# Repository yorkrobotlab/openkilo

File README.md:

# OpenKilo

This repository contains resources related to the OpenKilo Kilobot revision, which was designed to aid repair and extensibility of the Kilobot platform.

This project was possible due to the material made open-source by other institutions, most importantly [Harvard University](https://ssr.seas.harvard.edu/kilobots) and [Western Carolina University](https://kilobot.wcu.edu/).

## Contents

* [Hardware Design](Hardware%20Design/) - KiCad project and exported Gerber files used to produce this version of the Kilobot
* [Documentation](Documentation/) - hardware schematic (produced from Harvard and WCU designs), assembly and programming guides, and bill of materials
* [Photos and Video](Photos%20and%20Video/) - showing the completed robots and their usage

## Requirements

Our Overhead Controller (OHC) was built to a design by Western Carolina University (WCU). Their detailed guide was also used for the programming and control of both the OHC and Kilobots. For more details, refer to their material at https://kilobot.wcu.edu/.

In particular:

* OHC Gerber files
* Software folder including Kilobot and OHC firmware
* [KiloGUI](https://github.com/acornejo/kilogui), GUI application for Kilobot control
* [Maker: A Kilobot Swarm](https://www.asee.org/public/conferences/64/papers/15441/view)

### Editing the PCB
[KiCad EDA](http://kicad.org/) is a free open-source electronic CAD suite which was used to create the OpenKilo design. KiCad is required in order to make changes to the design, but the exported Gerber files are also available for use directly.

The included Kilobot.lib is required for certain symbols and footprints, and must be added to the KiCad project using the process described [here](https://forum.kicad.info/t/library-management-in-kicad-version-5/14636).

[freeRouting](https://freerouting.org/) was used in conjunction with KiCad to carry out automatic PCB routing for the current design.

## Build Process
1. Purchase all PCBs and required components using BOMs included here. For the OHC PCB, use WCU Gerber files.

2. Following the guide in [Maker: A Kilobot Swarm](https://www.asee.org/public/conferences/64/papers/15441/view), install the required software before assembling the OHC and programming its firmware.

3. Assemble the OpenKilo hardware using the included assembly diagram and checklists.

4. Continuing with the WCU guide, program Kilobot firmware using a 2x3 header cable. Connection details are given in [Programming Reference.pdf](Documentation/Programming%20Reference.pdf).

5. Install KiloGUI and use the OHC to program a benchmark test onto the OpenKilo robots. These tests can be found in the WCU materials as well as at [Kilobotics](https://www.kilobotics.com/labs) where details of their functions are available.

## Author
The main OpenKilo design and prototyping was completed by Jamie Trump while a postgraduate student in the [School of Engineering, Computing and Mathematics](https://www.plymouth.ac.uk/schools/school-of-engineering-computing-and-mathematics) at the [University of Plymouth](https://www.plymouth.ac.uk/).

His original project repository can be found at [github.com/jamie-trump/Plymouth-Kilobot-2019](https://github.com/jamie-trump/Plymouth-Kilobot-2019).

This work is licensed under a [Creative Commons Attribution-NonCommercial-ShareAlike 4.0 International License](http://creativecommons.org/licenses/by-nc-sa/4.0/).

## Links

### Information and Publications
* [Kilobot @ WCU](https://kilobot.wcu.edu/)
* [Maker: A Kilobot Swarm](https://www.asee.org/public/conferences/64/papers/15441/view)
* [Kilobotics Labs](https://www.kilobotics.com/labs)

### Software
* [KiloGUI](https://github.com/acornejo/kilogui)
* [KiCad EDA](http://kicad.org/)
* [freeRouting](https://freerouting.org/)

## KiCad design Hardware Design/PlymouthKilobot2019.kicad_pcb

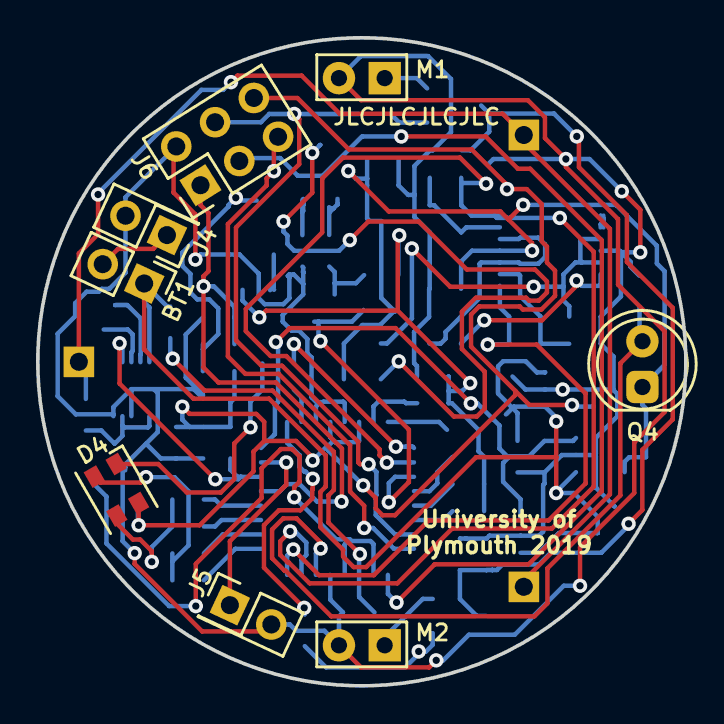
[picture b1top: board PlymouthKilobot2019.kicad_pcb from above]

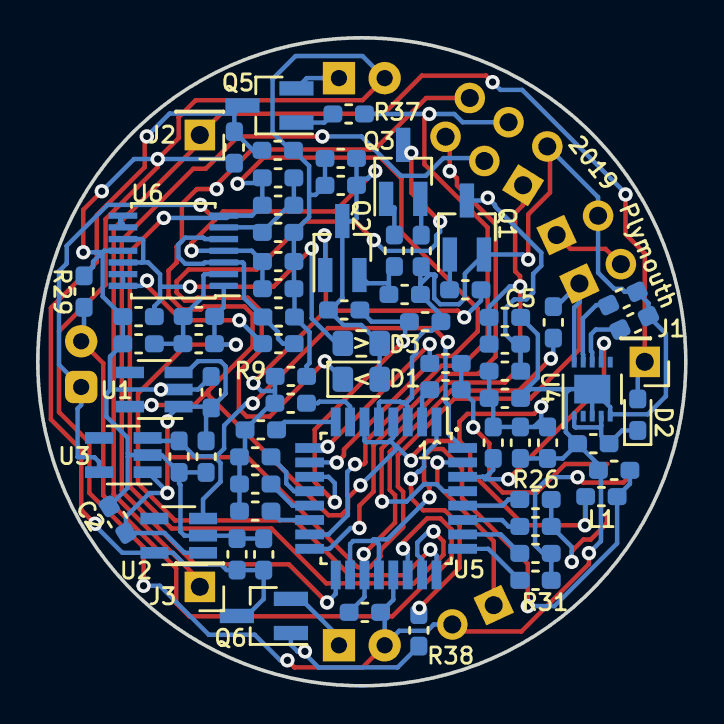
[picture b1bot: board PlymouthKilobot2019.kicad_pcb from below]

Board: 2 copper layers, 36.0 x 36.0 mm, 81 parts (73 on the bottom side), 55 nets.

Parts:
BT1: 3.3; PinHeader_1x02_P2.54mm_Vertical
C1, C2, C3, C4, C6, C7, C9, C12, C19, C20: 2.2u; C_0603_1608Metric_Pad1.05x0.95mm_HandSolder
C5, C8, C10, C14, C17, C18: 0.01u; C_0603_1608Metric_Pad1.05x0.95mm_HandSolder
C11: 0.1u; C_0603_1608Metric_Pad1.05x0.95mm_HandSolder
C13: 1n; C_0603_1608Metric_Pad1.05x0.95mm_HandSolder
C15, C16: 68p; C_0603_1608Metric_Pad1.05x0.95mm_HandSolder
D1: IR_LED; LED_0805_2012Metric_Pad1.15x1.40mm_HandSolder
D2: D_Schottky; D_0603_1608Metric_Pad1.05x0.95mm_HandSolder
D3: TEMD7100X01; R_0805_2012Metric_Pad1.15x1.40mm_HandSolder
D4: LED_RGBA; LED_Cree-PLCC4_3.2x2.8mm_CCW
J1: Leg 1; PinHeader_1x01_P2.54mm_Vertical
J2: Leg 2; PinHeader_1x01_P2.54mm_Vertical
J3: Leg 3; PinHeader_1x01_P2.54mm_Vertical
J4: Power; PinHeader_2x01_P2.54mm_Vertical
J5: Debug; PinHeader_2x01_P2.54mm_Vertical
J6: Program; PinHeader_2x03_P2.54mm_Vertical
L1: 10u; L_0603_1608Metric_Pad1.05x0.95mm_HandSolder
M1, M2: VIB_MOTOR; Vibration_Motor_10x2mm_Vert_noBody
Q1, Q5, Q6: MMBT6428; SOT-23_Handsoldering
Q2, Q3: 2SD2114KT146W; SOT-23_Handsoldering__pins_changed
Q4: TEPT5700; LED_D5.0mm_Clear
R1: 154; R_0603_1608Metric_Pad1.05x0.95mm_HandSolder
R2: 1.18k; R_0603_1608Metric_Pad1.05x0.95mm_HandSolder
R3: 2.37k; R_0603_1608Metric_Pad1.05x0.95mm_HandSolder
R4: 4.87k; R_0603_1608Metric_Pad1.05x0.95mm_HandSolder
R5: 9.76k; R_0603_1608Metric_Pad1.05x0.95mm_HandSolder
R6, R20, R21: 10k; R_0603_1608Metric_Pad1.05x0.95mm_HandSolder
R8: 4.99k; R_0603_1608Metric_Pad1.05x0.95mm_HandSolder
R9: 301; R_0603_1608Metric_Pad1.05x0.95mm_HandSolder
R10: 11k; R_0603_1608Metric_Pad1.05x0.95mm_HandSolder
R11: 806; R_0603_1608Metric_Pad1.05x0.95mm_HandSolder
R12: 1.62k; R_0603_1608Metric_Pad1.05x0.95mm_HandSolder
R13: 10; R_0603_1608Metric_Pad1.05x0.95mm_HandSolder
R14: 0.82; R_0603_1608Metric_Pad1.05x0.95mm_HandSolder
R15, R16: 2M; R_0603_1608Metric_Pad1.05x0.95mm_HandSolder
R17: 20k; R_0603_1608Metric_Pad1.05x0.95mm_HandSolder
R18: 1.47k; R_0603_1608Metric_Pad1.05x0.95mm_HandSolder
R19, R35: 25.5k; R_0603_1608Metric_Pad1.05x0.95mm_HandSolder
R24: 549k; R_0603_1608Metric_Pad1.05x0.95mm_HandSolder
R25: 5.62k; R_0603_1608Metric_Pad1.05x0.95mm_HandSolder
R26, R27, R28: 1.6k; R_0603_1608Metric_Pad1.05x0.95mm_HandSolder
R29: 604k; R_0603_1608Metric_Pad1.05x0.95mm_HandSolder
R30, R31, R32: 820; R_0603_1608Metric_Pad1.05x0.95mm_HandSolder
R33: 2.26k; R_0603_1608Metric_Pad1.05x0.95mm_HandSolder
R34: 499; R_0603_1608Metric_Pad1.05x0.95mm_HandSolder
R36: 280k; R_0603_1608Metric_Pad1.05x0.95mm_HandSolder
R37, R38: 200; R_0603_1608Metric_Pad1.05x0.95mm_HandSolder
U1: XC6221B302MR-G; SOT-23-5_HandSoldering
U2, U3: XC6210B302MR-G; SOT-23-5_HandSoldering
U4: LM3658SD-A; WSON-10-1EP_3x3mm_P0.5mm_EP0.6x2.5mm
U5: ATmega48A-AU; TQFP-32_7x7mm_P0.8mm
U6: OPA4376AIPWR; TSSOP-14_4.4x5mm_P0.65mm_altered

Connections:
+BATT: BT1.1, C1.2, C2.2, C3.2, R15.2, U1.1, U1.3, U2.1, U3.1, U4.10
AMP1_OUT: C15.1, R35.1, U5.24, U6.1
AMP2_OUT: C16.1, R36.1, U5.10, U5.23, U6.7
BATT: R15.1, R16.2, U5.19
BLU_HI: R30.1, U5.27
BLU_LO: R26.1, U5.28
CE: R6.2, U2.3, U3.3, U5.32
CHARGE: R20.2, U4.7, U5.30
DEBUG: J5.1, U5.31
GNDREF: C1.1, C2.1, C3.1, C4.1, C5.1, C6.2, C7.1, C8.1, C9.2, C10.2, C11.2, C12.1, C14.1, C17.1, C18.1, C19.1, C20.1, J4.2, J5.2, J6.2, M1.2, M2.2, Q1.2, R6.1, R9.2, R11.2, R14.2, R16.1, R18.1, R19.1, R21.1, R24.2, R25.2, R29.2, R33.1, R34.1, U1.2, U2.2, U3.2, U4.3, U4.5, U4.11, U5.3, U5.5, U5.21, U6.11
GRN_HI: R31.1, U5.25
GRN_LO: R27.1, U5.26
LIGHT: Q4.2, R29.1, U5.22
MISO: J6.5, U5.16
MOSI: J6.4, R37.1, U5.15
unnamed: BT1.2, J4.1
unnamed: C6.1, D2.1, U4.1, U4.4
unnamed: C11.1, L1.2, U5.18, U5.20
unnamed: C13.1, R25.1, U6.3, U6.5
unnamed: C13.2, U6.13, U6.14
unnamed: C15.2, R33.2, R35.2, U6.2
unnamed: C16.2, R34.2, R36.2, U6.6
unnamed: D1.1, Q3.3
unnamed: D2.2, J1.1, J2.1, J3.1
unnamed: D3.2, R24.1, U6.10, U6.12
unnamed: D4.1, R28.2, R32.2
unnamed: D4.2, R27.2, R31.2
unnamed: D4.3, R26.2, R30.2
unnamed: M1.1, Q5.2
unnamed: M2.1, Q6.2
unnamed: Q1.1, R8.1
unnamed: Q1.3, R10.2, R12.2
unnamed: Q2.1, R11.1, R13.1
unnamed: Q3.1, R14.1
unnamed: Q3.2, R13.2
unnamed: Q5.1, R37.2
unnamed: Q6.1, R38.2
unnamed: R19.2, U4.8
unnamed: R21.2, U4.9
unnamed: U6.8, U6.9
PB0: R1.2, U5.12
PB1: R2.2, U5.13
PB2: R3.2, U5.14
PB6: R4.2, U5.7
PB7: R5.2, U5.8
PD3: R38.1, U5.1
PD7: R17.1, R18.2, U5.11
RED_HI: R32.1, U5.2
RED_LO: R28.1, U5.9
RESET: C5.2, J6.1, R12.1, U5.29
SCK: J6.3, U5.17
TX: Q2.2, R1.1, R2.1, R3.1, R4.1, R5.1, R8.2, R9.1
V1: C4.2, C9.1, C10.1, D4.4, J6.6, L1.1, R10.1, R20.1, U1.5, U5.4, U5.6
V2: C17.2, C18.2, C19.2, C20.2, Q5.3, Q6.3, U2.5
V3: C7.2, C8.2, C12.2, C14.2, D1.2, D3.1, Q2.3, Q4.1, R17.2, U3.5, U6.4

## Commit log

2020-05-18 Added CC BY-NC-SA 4.0 licence
    This is compatible with the original Kilobot CC BY-NC-SA 3.0 licence, on
    which this work is based.
2020-05-18 Added KiCad hardware design files and Gerber files
    Expanded from the zip files, which have now been removed.
2021-11-10 Update README.md
    https://forum.kicad.info/t/warning-avoid-all-links-to-kicad-pcb-org-use-kicad-org/31521
